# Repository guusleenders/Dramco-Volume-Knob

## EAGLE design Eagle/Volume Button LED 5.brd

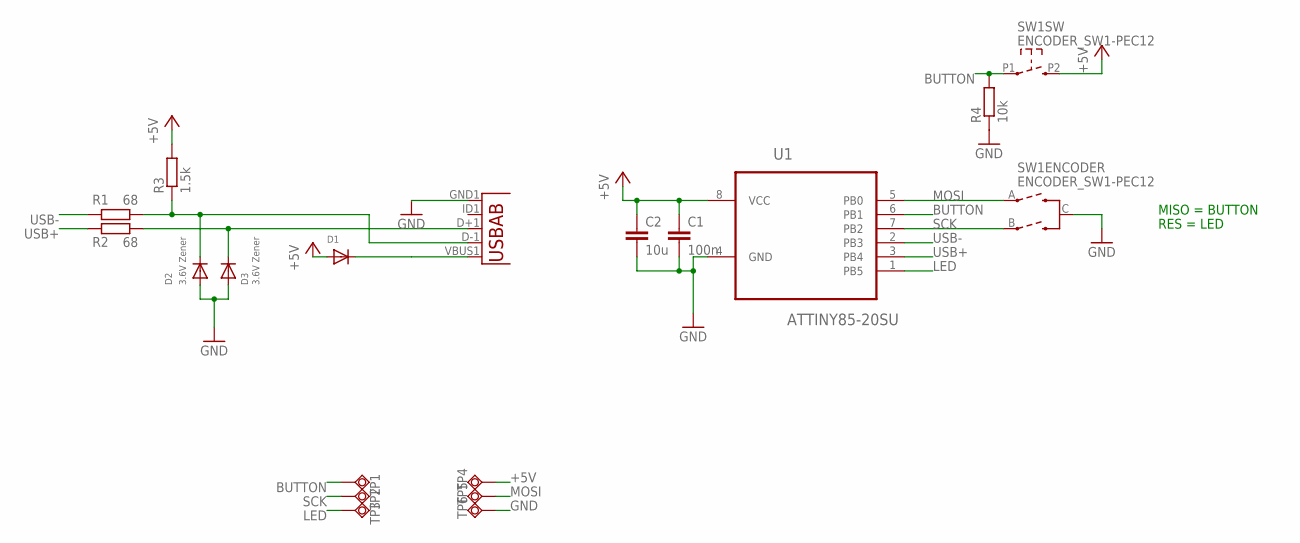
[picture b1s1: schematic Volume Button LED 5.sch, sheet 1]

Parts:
C1: 100n; C0805
C2: 10u; C0805
D1: DIODESOD-123; SOD-123
D2, D3: 3.6V Zener; SOD-323F
R1, R2: 68; R0603
R3: 1.5k; R0603
R4: 10k; R0805
SW1: ENCODER_SW1-PEC12; PEC12_INCREMENTAL_ENCODER
TP1, TP2, TP3, TP4, TP5, TP6: TPSQTP15R; TP15R
U1: ATTINY85-20SU; SOIC127P798X216-8N
U2: USB""; USB-MICRO-SMD

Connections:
+5V: C1.1, C2.1, D1.A, R3.2, SW1.P2 (2), TP4.TP, U1.8 (VCC); also elsewhere on the board
BUTTON: R4.2, SW1.P1 (1), TP1.TP, U1.6 (PB1)
GND: C1.2, C2.2, D2.A, D3.A, R4.1, SW1.C, TP6.TP, U1.4 (GND), U2.GND1 (GND); also elsewhere on the board
LED: TP3.TP, U1.1 (PB5); also elsewhere on the board
MOSI: SW1.A, TP5.TP, U1.5 (PB0)
unnamed: D1.C, U2.VBUS1 (VBUS)
unnamed: D2.C, R1.1, R3.1, U2.D-1 (D-)
unnamed: D3.C, R2.1, U2.D+1 (D+)
SCK: SW1.B, TP2.TP, U1.7 (PB2)
USB+: R2.2, U1.3 (PB4)
USB-: R1.2, U1.2 (PB3)

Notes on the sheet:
MISO = BUTTON
RES = LED

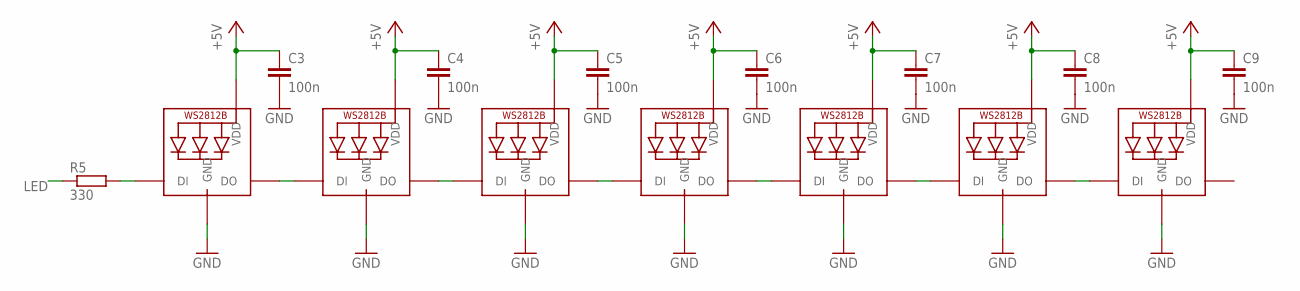
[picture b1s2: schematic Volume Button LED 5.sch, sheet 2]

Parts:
C3, C4, C5, C6, C7, C8, C9: 100n; C0805
LED1, LED2, LED3, LED4, LED5, LED6, LED7: WS2812B5050; WS2812B
R5: 330; R0805

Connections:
+5V: C3.1, C4.1, C5.1, C6.1, C7.1, C8.1, C9.1, LED1.1-VDD (VDD), LED2.1-VDD (VDD), LED3.1-VDD (VDD), LED4.1-VDD (VDD), LED5.1-VDD (VDD), LED6.1-VDD (VDD), LED7.1-VDD (VDD); also elsewhere on the board
GND: C3.2, C4.2, C5.2, C6.2, C7.2, C8.2, C9.2, LED1.3-GND (GND), LED2.3-GND (GND), LED3.3-GND (GND), LED4.3-GND (GND), LED5.3-GND (GND), LED6.3-GND (GND), LED7.3-GND (GND); also elsewhere on the board
LED: R5.1; also elsewhere on the board
unnamed: LED1.2-DOUT (DO), LED2.4-DIN (DI)
unnamed: LED1.4-DIN (DI), R5.2
unnamed: LED2.2-DOUT (DO), LED3.4-DIN (DI)
unnamed: LED3.2-DOUT (DO), LED4.4-DIN (DI)
unnamed: LED4.2-DOUT (DO), LED5.4-DIN (DI)
unnamed: LED5.2-DOUT (DO), LED6.4-DIN (DI)
unnamed: LED6.2-DOUT (DO), LED7.4-DIN (DI)

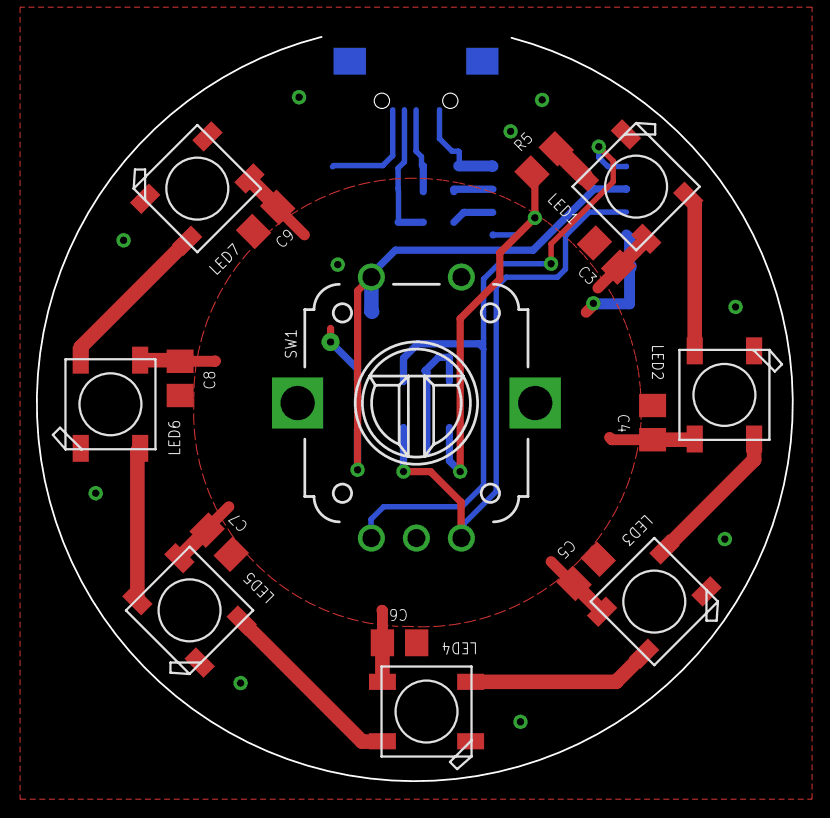
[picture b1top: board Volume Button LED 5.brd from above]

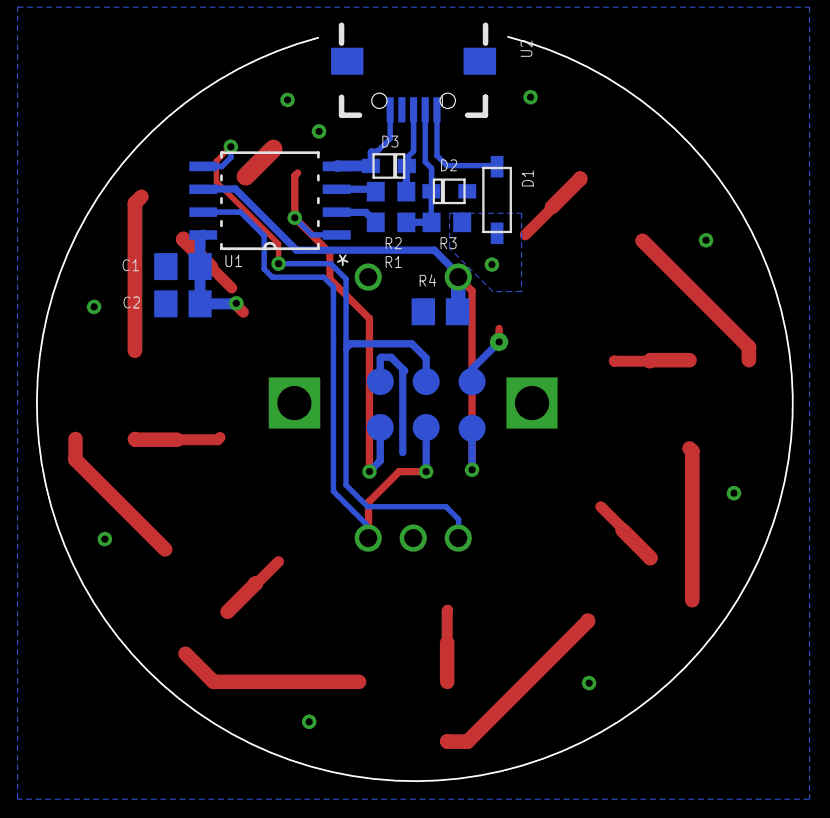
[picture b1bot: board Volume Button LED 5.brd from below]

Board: 2 copper layers, 42.0 x 41.3 mm, 33 parts (17 on the bottom side), 18 nets.

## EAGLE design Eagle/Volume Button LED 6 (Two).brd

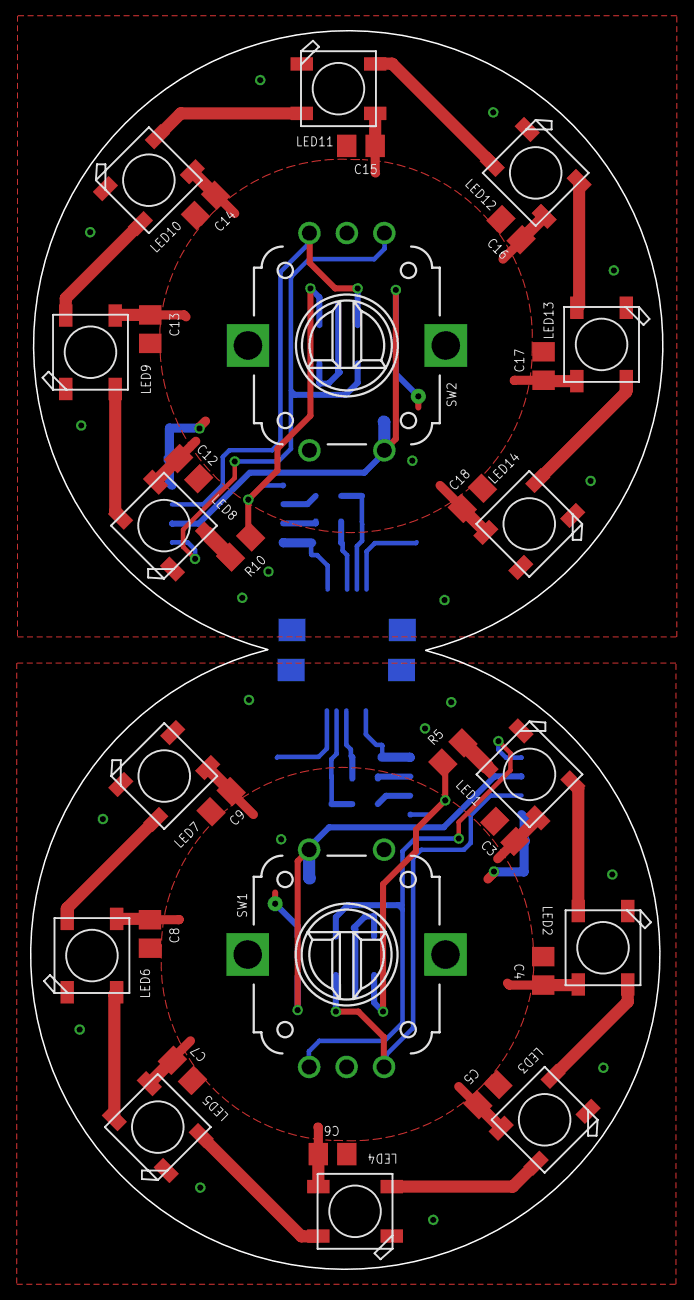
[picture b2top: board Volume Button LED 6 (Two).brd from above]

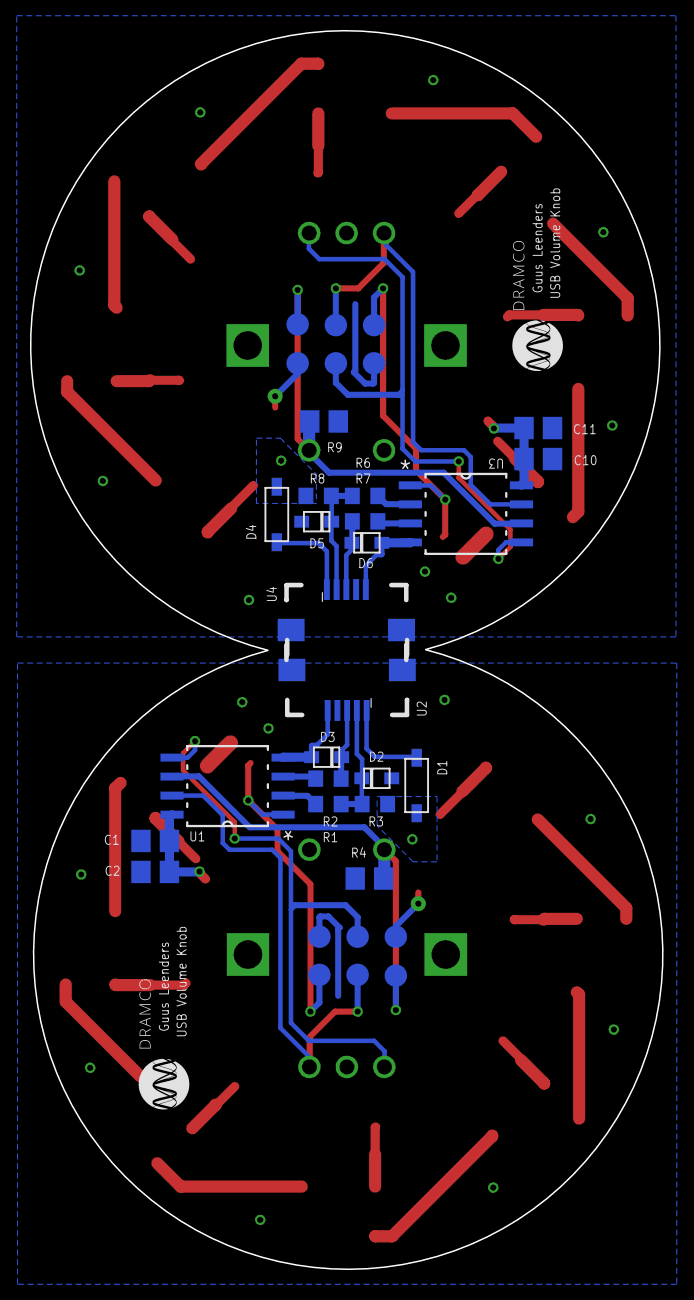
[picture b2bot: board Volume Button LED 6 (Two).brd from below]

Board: 2 copper layers, 42.2 x 82.7 mm, 66 parts (34 on the bottom side), 36 nets.

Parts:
C1, C3, C4, C5, C6, C7, C8, C9, C10, C12, C13, C14, C15, C16, C17, C18: 100n; C0805
C2, C11: 10u; C0805
D1, D4: SOD-123
D2, D3, D5, D6: 3.6V Zener; SOD-323F
LED1, LED2, LED3, LED4, LED5, LED6, LED7, LED8, LED9, LED10, LED11, LED12, LED13, LED14: WS2812B5050; WS2812B
R1, R2, R6, R7: 68; R0603
R3, R8: 1.5k; R0603
R4, R9: 10k; R0805
R5, R10: 330; R0805
SW1, SW2: ENCODER_SW1-PEC12; PEC12_INCREMENTAL_ENCODER
TP1, TP2, TP3, TP4, TP5, TP6, TP7, TP8, TP9, TP10, TP11, TP12: TPSQTP15R; TP15R
U1, U3: ATTINY85-20SU; SOIC127P798X216-8N
U2, U4: USB-MICRO-SMD

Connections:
+5V: C1.1, C2.1, C3.1, C4.1, C5.1, C6.1, C7.1, C8.1, C9.1, D1.A, LED1.1-VDD, LED2.1-VDD, LED3.1-VDD, LED4.1-VDD, LED5.1-VDD, LED6.1-VDD, LED7.1-VDD, R3.2, SW1.P2, TP4.TP, U1.8
+5V1: C10.1, C11.1, C12.1, C13.1, C14.1, C15.1, C16.1, C17.1, C18.1, D4.A, LED8.1-VDD, LED9.1-VDD, LED10.1-VDD, LED11.1-VDD, LED12.1-VDD, LED13.1-VDD, LED14.1-VDD, R8.2, SW2.P2, TP10.TP, U3.8
BUTTON: R4.2, SW1.P1, TP1.TP, U1.6
BUTTON1: R9.2, SW2.P1, TP7.TP, U3.6
GND: C1.2, C2.2, C3.2, C4.2, C5.2, C6.2, C7.2, C8.2, C9.2, D2.A, D3.A, LED1.3-GND, LED2.3-GND, LED3.3-GND, LED4.3-GND, LED5.3-GND, LED6.3-GND, LED7.3-GND, R4.1, SW1.C, TP6.TP, U1.4, U2.GND1
GND1: C10.2, C11.2, C12.2, C13.2, C14.2, C15.2, C16.2, C17.2, C18.2, D5.A, D6.A, LED8.3-GND, LED9.3-GND, LED10.3-GND, LED11.3-GND, LED12.3-GND, LED13.3-GND, LED14.3-GND, R9.1, SW2.C, TP12.TP, U3.4, U4.GND1
LED: R5.1, TP3.TP, U1.1
LED1: R10.1, TP9.TP, U3.1
MOSI: SW1.A, TP5.TP, U1.5
MOSI1: SW2.A, TP11.TP, U3.5
unnamed: LED1.2-DOUT, LED2.4-DIN
unnamed: D1.C, U2.VBUS1
unnamed: D2.C, R1.1, R3.1, U2.D-1
unnamed: D3.C, R2.1, U2.D+1
unnamed: LED1.4-DIN, R5.2
unnamed: D4.C, U4.VBUS1
unnamed: LED2.2-DOUT, LED3.4-DIN
unnamed: LED3.2-DOUT, LED4.4-DIN
unnamed: LED4.2-DOUT, LED5.4-DIN
unnamed: LED5.2-DOUT, LED6.4-DIN
unnamed: D5.C, R6.1, R8.1, U4.D-1
unnamed: LED6.2-DOUT, LED7.4-DIN
unnamed: D6.C, R7.1, U4.D+1
unnamed: LED8.2-DOUT, LED9.4-DIN
unnamed: LED9.2-DOUT, LED10.4-DIN
unnamed: LED10.2-DOUT, LED11.4-DIN
unnamed: LED11.2-DOUT, LED12.4-DIN
unnamed: LED12.2-DOUT, LED13.4-DIN
unnamed: LED13.2-DOUT, LED14.4-DIN
unnamed: LED8.4-DIN, R10.2
SCK: SW1.B, TP2.TP, U1.7
SCK1: SW2.B, TP8.TP, U3.7
USB+: R2.2, U1.3
USB+1: R7.2, U3.3
USB-: R1.2, U1.2
USB-1: R6.2, U3.2

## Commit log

2017-03-30 :space_invader: Added .gitattributes
2017-03-30 First commit
    First commit
2017-03-30 Atom platformio compatible
2017-03-31 Add readme
2017-03-31 Added arduino folder for arduino IDE
2017-03-31 Added long press function
    working
    -lights dont work
    -short press playpause
    -long press next song
2018-08-14 changes for knob Bart
